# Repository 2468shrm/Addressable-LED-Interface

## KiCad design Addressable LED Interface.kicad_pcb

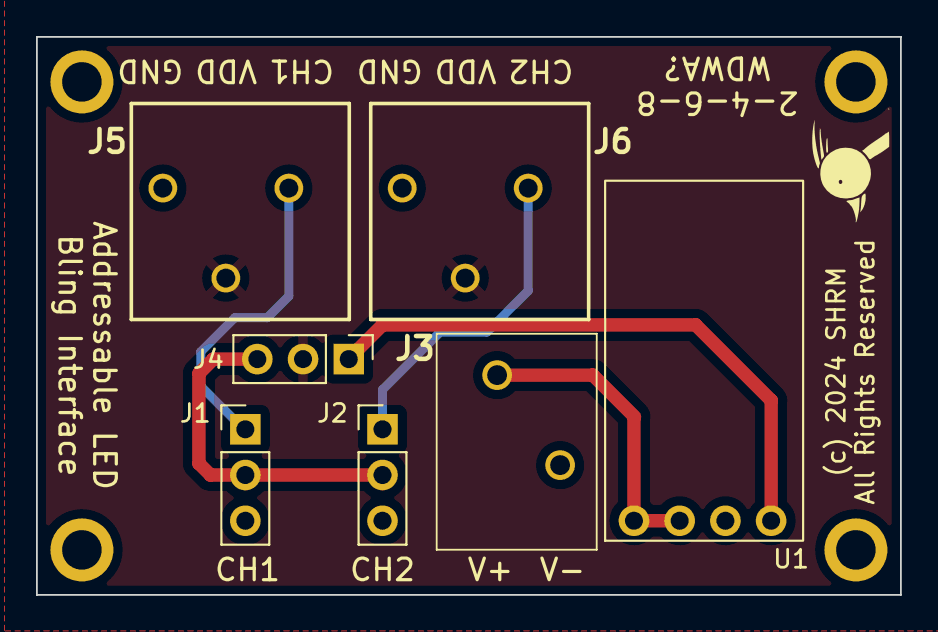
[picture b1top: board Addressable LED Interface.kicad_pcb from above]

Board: 2 copper layers, 48.0 x 31.0 mm, 11 parts (0 on the bottom side), 7 nets.

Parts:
H1, H2, H3, H4: MountingHole_Pad; MountingHole_2.2mm_M2_ISO7380_Pad
J1, J2, J4: Conn_01x03; PinHeader_1x03_P2.54mm_Vertical
J3: 250-202; 250202
J5, J6: 250-203; 250-203_1
U1: Weewooday-820

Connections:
+5V: J4.1, U1.4 (VOUT)
+6V: J1.2, J2.2, J4.3
+BATT: J3.1, U1.1 (EN), U1.2 (VIN)
/CH1: J1.1, J5.1
/CH2: J2.1, J6.1
GND: J1.3, J2.3, J3.2, J5.3, J6.3, U1.3 (GND)
VDD: J4.2, J5.2, J6.2

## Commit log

2024-02-24 PCB files

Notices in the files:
Addressable LED Interface.kicad_pcb:
(c) 2024 SHRM
All Rights Reserved
